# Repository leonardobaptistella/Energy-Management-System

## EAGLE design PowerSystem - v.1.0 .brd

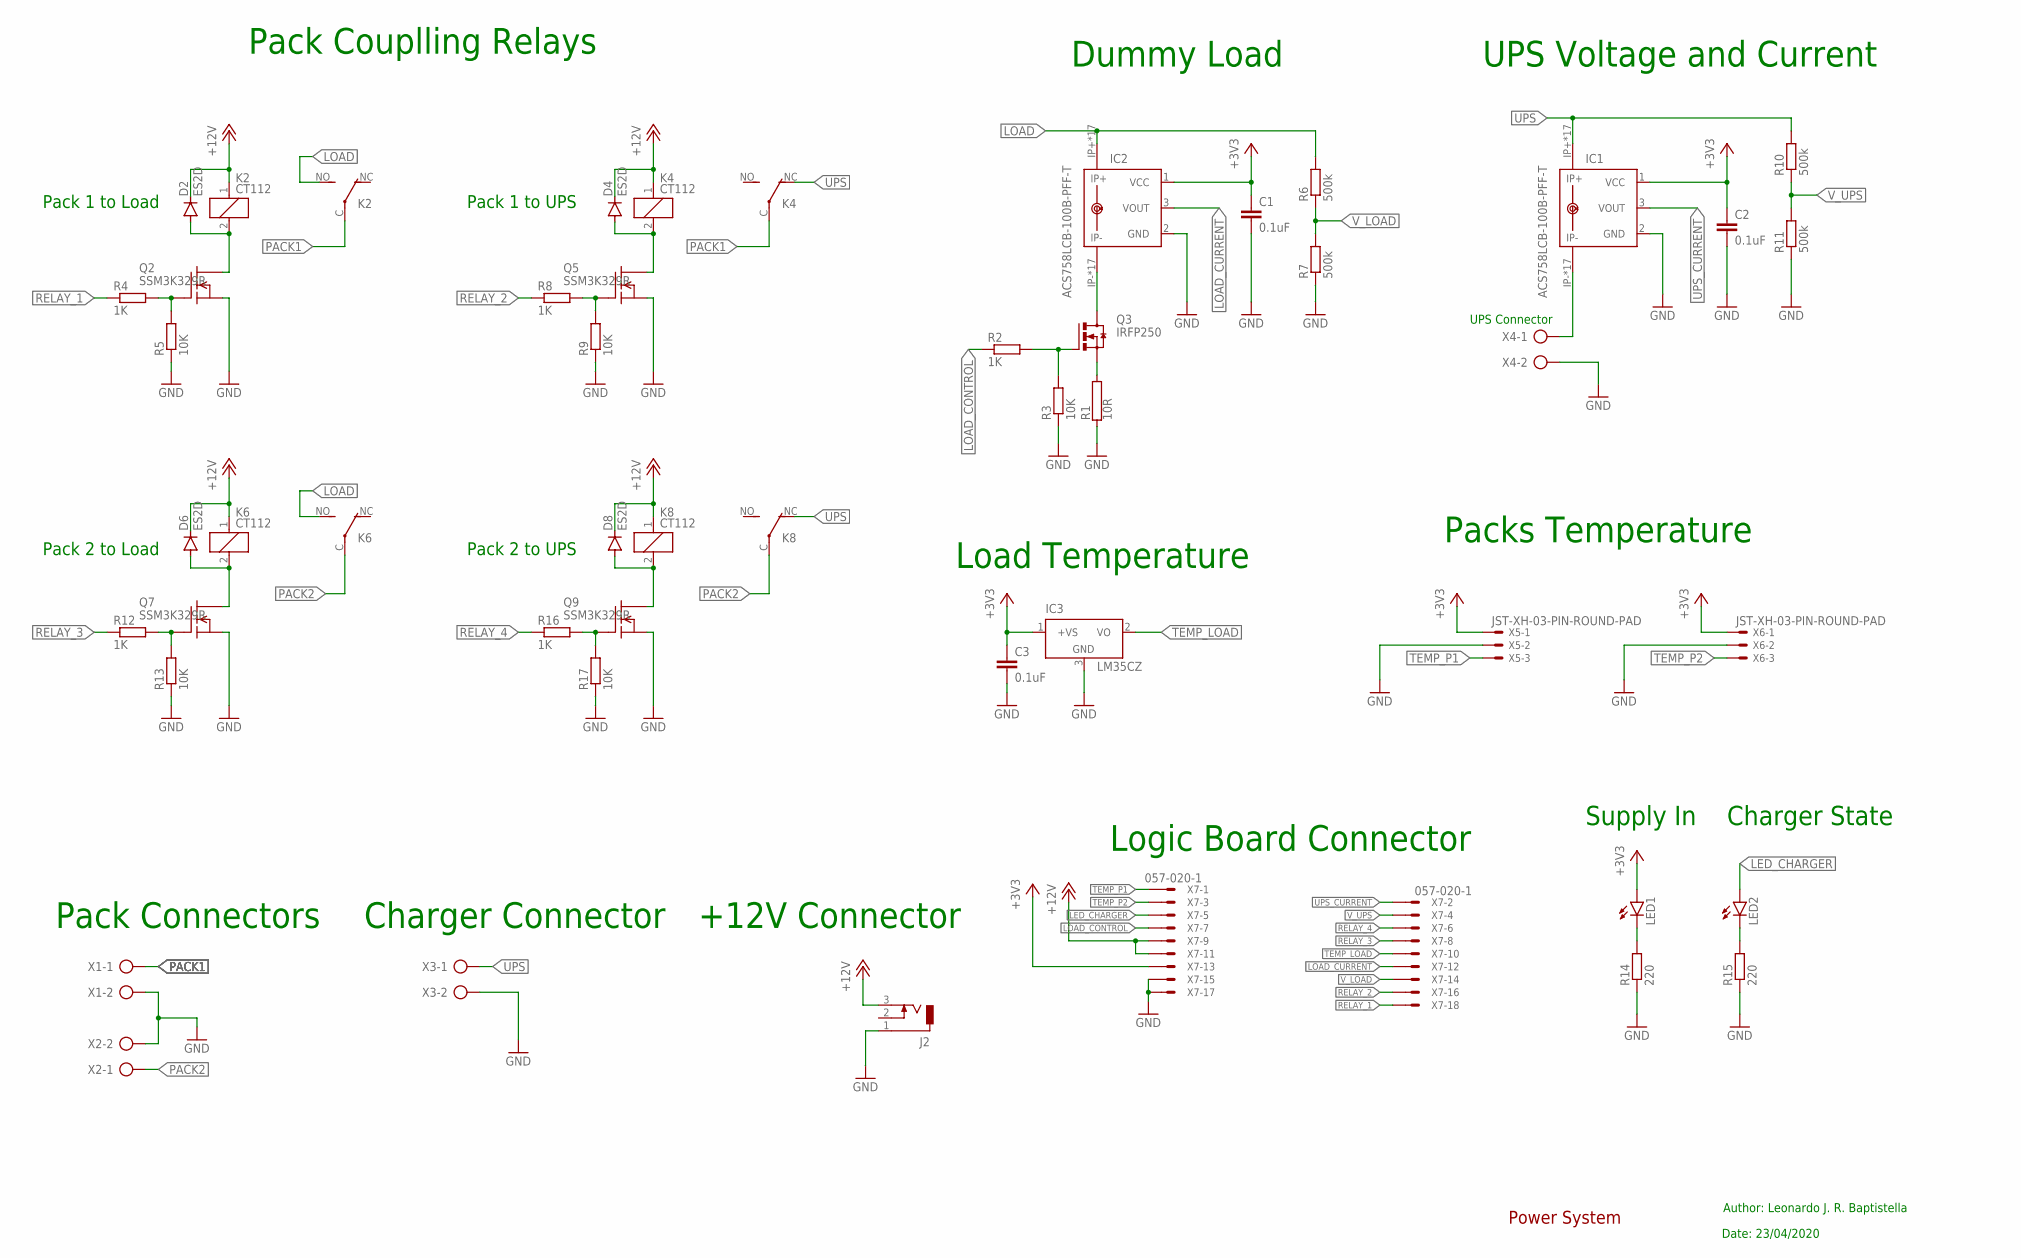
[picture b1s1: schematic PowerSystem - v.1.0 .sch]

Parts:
C1, C2, C3: 0.1uF; C1206
D2, D4, D6, D8: ES2D; SMB
IC1, IC2: ACS758LCB-100B-PFF-T; CB-PFF
IC3: LM35CZ; TO92
J2: DCJ0303
K2, K4, K6, K8: CT112; CT-SLIM
LED1, LED2: LEDCHIPLED_1206; CHIPLED_1206
Q2, Q5, Q7, Q9: SSM3K329R; SOT23
Q3: IRFP250; TO-247AD-V
R1: 10R; HS25
R2, R4, R8, R12, R16: 1K; R1206
R3, R5, R9, R13, R17: 10K; R1206
R6, R7, R10, R11: 500k; R1206
R14, R15: 220; R1206
X1, X2, X3, X4: AK500/2-H
X5, X6: JST-XH-03-PIN-ROUND-PAD; JST-XH-03-PACKAGE-ROUND-PAD
X7: 057-020-1

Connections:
+3V3: C1.1, C2.1, C3.1, IC1.1 (VCC), IC2.1 (VCC), IC3.1 (+VS), LED1.A, X5.1, X6.1, X7.13
+12V: D2.C, D4.C, D6.C, D8.C, J2.3, K2.1, K4.1, K6.1, K8.1, X7.9, X7.11
GND: C1.2, C2.2, C3.2, IC1.2 (GND), IC2.2 (GND), IC3.3 (GND), J2.1, Q2.2 (S), Q5.2 (S), Q7.2 (S), Q9.2 (S), R1.1, R3.1, R5.1, R7.1, R9.1, R11.1, R13.1, R14.1, R15.1, R17.1, X1.2, X2.2, X3.2, X4.2, X5.2, X6.2, X7.15, X7.17
LED_CHARGER: LED2.A, X7.5
LOAD: IC2.IP+, IC2.IP+@2 (IP+), IC2.IP+@3 (IP+), IC2.IP+@4 (IP+), IC2.IP+@5 (IP+), IC2.IP+@6 (IP+), IC2.IP+@7 (IP+), IC2.IP+@8 (IP+), IC2.IP+@9 (IP+), IC2.IP+@10 (IP+), IC2.IP+@11 (IP+), IC2.IP+@12 (IP+), IC2.IP+@13 (IP+), IC2.IP+@14 (IP+), IC2.IP+@15 (IP+), IC2.IP+@16 (IP+), IC2.IP+@17 (IP+), K2.NO (S), K6.NO (S), R6.2
LOAD_CONTROL: R2.1, X7.7
LOAD_CURRENT: IC2.3 (VOUT), X7.12
unnamed: Q3.S, R1.2
unnamed: Q2.1 (G), R4.2, R5.2
unnamed: Q3.G, R2.2, R3.2
unnamed: D2.A, K2.2, Q2.3 (D)
unnamed: IC2.IP-, IC2.IP-@2 (IP-), IC2.IP-@3 (IP-), IC2.IP-@4 (IP-), IC2.IP-@5 (IP-), IC2.IP-@6 (IP-), IC2.IP-@7 (IP-), IC2.IP-@8 (IP-), IC2.IP-@9 (IP-), IC2.IP-@10 (IP-), IC2.IP-@11 (IP-), IC2.IP-@12 (IP-), IC2.IP-@13 (IP-), IC2.IP-@14 (IP-), IC2.IP-@15 (IP-), IC2.IP-@16 (IP-), IC2.IP-@17 (IP-), Q3.D
unnamed: Q5.1 (G), R8.2, R9.2
unnamed: D4.A, K4.2, Q5.3 (D)
unnamed: IC1.IP-, IC1.IP-@2 (IP-), IC1.IP-@3 (IP-), IC1.IP-@4 (IP-), IC1.IP-@5 (IP-), IC1.IP-@6 (IP-), IC1.IP-@7 (IP-), IC1.IP-@8 (IP-), IC1.IP-@9 (IP-), IC1.IP-@10 (IP-), IC1.IP-@11 (IP-), IC1.IP-@12 (IP-), IC1.IP-@13 (IP-), IC1.IP-@14 (IP-), IC1.IP-@15 (IP-), IC1.IP-@16 (IP-), IC1.IP-@17 (IP-), X4.1
unnamed: LED2.C, R15.2
unnamed: Q7.1 (G), R12.2, R13.2
unnamed: D6.A, K6.2, Q7.3 (D)
unnamed: LED1.C, R14.2
unnamed: Q9.1 (G), R16.2, R17.2
unnamed: D8.A, K8.2, Q9.3 (D)
PACK1: K2.C, K4.C, X1.1
PACK2: K6.C, K8.C, X2.1
RELAY_1: R4.1, X7.18
RELAY_2: R8.1, X7.16
RELAY_3: R12.1, X7.8
RELAY_4: R16.1, X7.6
TEMP_LOAD: IC3.2 (VO), X7.10
TEMP_P1: X5.3, X7.1
TEMP_P2: X6.3, X7.3
UPS: IC1.IP+, IC1.IP+@2 (IP+), IC1.IP+@3 (IP+), IC1.IP+@4 (IP+), IC1.IP+@5 (IP+), IC1.IP+@6 (IP+), IC1.IP+@7 (IP+), IC1.IP+@8 (IP+), IC1.IP+@9 (IP+), IC1.IP+@10 (IP+), IC1.IP+@11 (IP+), IC1.IP+@12 (IP+), IC1.IP+@13 (IP+), IC1.IP+@14 (IP+), IC1.IP+@15 (IP+), IC1.IP+@16 (IP+), IC1.IP+@17 (IP+), K4.NC (O), K8.NC (O), R10.2, X3.1
UPS_CURRENT: IC1.3 (VOUT), X7.2
V_LOAD: R6.1, R7.2, X7.14
V_UPS: R10.1, R11.2, X7.4

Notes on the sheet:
Pack Couplling Relays
Dummy Load
Pack Connectors
Pack 1 to Load
Pack 1 to UPS
Pack 2 to Load
Pack 2 to UPS
Charger Connector
UPS Connector
UPS Voltage and Current
Packs Temperature
+12V Connector
Load Temperature
Supply In
Charger State
Logic Board Connector
Author: Leonardo J. R. Baptistella
Date: 23/04/2020
Power System

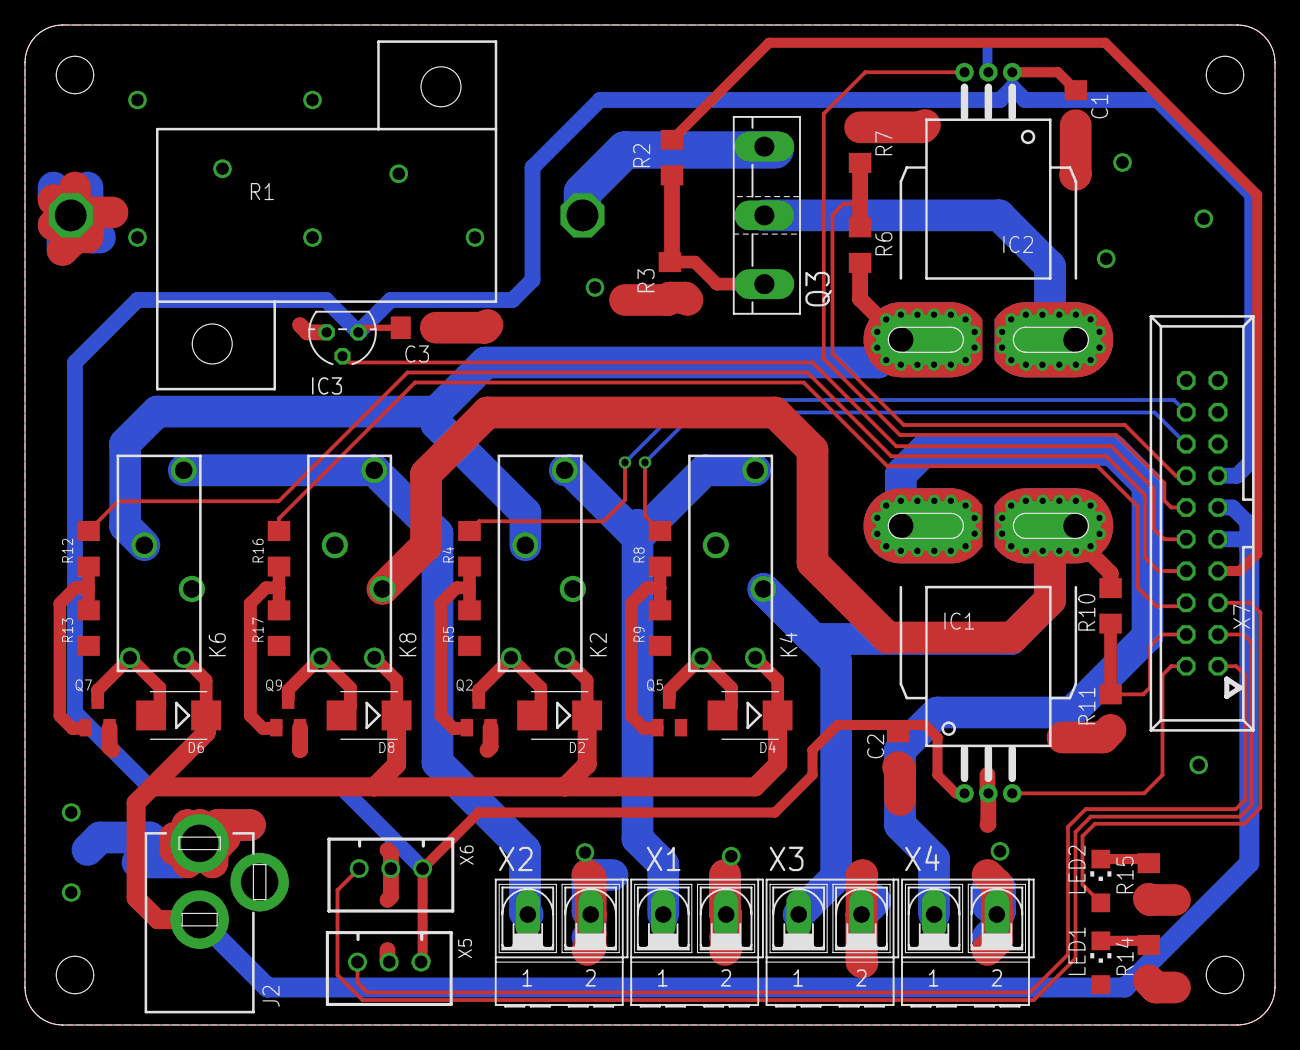
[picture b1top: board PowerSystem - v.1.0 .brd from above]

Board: 2 copper layers, 100.0 x 80.0 mm, 46 parts (0 on the bottom side), 34 nets.

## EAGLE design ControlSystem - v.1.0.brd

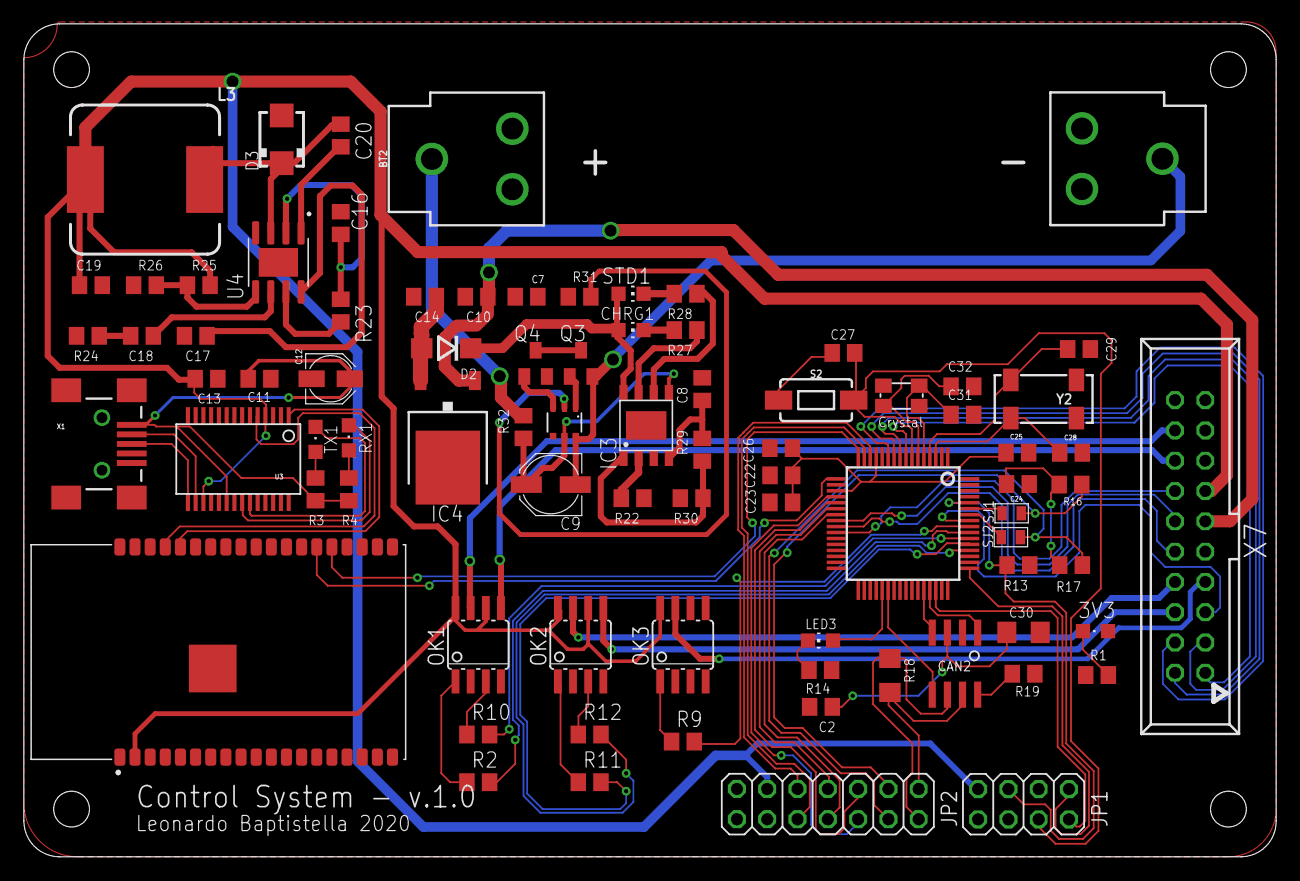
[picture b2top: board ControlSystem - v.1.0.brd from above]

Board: 2 copper layers, 105.0 x 69.8 mm, 82 parts (0 on the bottom side), 85 nets.

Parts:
3V3: CHIPLED_0805
A1: ESP32-WROVER-I; XCVR_ESP32-WROVER-I
BT2: BATTERY_18650-HOLDER
C2, C22, C23, C24, C25, C26, C27, C28, C29, C31, C32: C0805
C7: 10uf; C0805
C8, C10, C14, C16: 10uF; C0805
C9: 0.1uF; PANASONIC_C
C11, C13, C17: 0.1uF; C0805
C12: 10uF; PANASONIC_B
C18: 3.9nF; C0805
C19: 22uF; C0805
C20: 10nF; C0805
C30: 1nF; C1206
CAN2: SN65HVD233D; SOIC8
CHRG1: CHIP-LED0805
COMM_MICRO1: STM32L496RGT6; LQFP64_10X10
D2: DO214BA
D3: B130-13-F; SMA
IC3: TP4056; SOP-8
IC4: 7806DT; TO252
JP1: 2X04
JP2: 2X07
L3: SRR1280
LED3: CHIP-LED0805
OK1, OK2, OK3: ILD205; SOIC08
Q3, Q4: SSM3K329R; SOT23
R1: 220; R0805
R2, R3, R4, R9, R10, R11, R12: 1K; R0805
R13, R14, R16, R17, R22, R29, R30: R0805
R18: 120; R1206
R19, R32: 100; R0805
R23: 100K; R0805
R24: 6.8K; R0805
R25: 26.1K; R0805
R26: 10K; R0805
R27, R28, R31: 1k; R0805
RX1: Green; CHIPLED_0805
S2: MOMENTARY-SWITCH-SPST-SMD-6.0X3.5MM; TACTILE_SWITCH_SMD_6.0X3.5MM
SJ1, SJ2: SMD-JUMPER-2
STD1: CHIP-LED0805
TX1: Red; CHIPLED_0805
U3: FT232RLSSOP; SSOP28DB
U4: MP2307DN-LF-Z; SOIC127P600X170-9N
U$2: CRYSTAL; CRYSTAL_SMD
U$3: DW01; SOT23-6
X1: USB-SMD-NS; USB-MINIB-NOSTOP
X7: 057-020-1
Y2: CRYSTAL_8X3.8

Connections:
+3V3: 3V3.A, A1.2, C2.1, C13.1, C19.1, C22.1, C23.1, C24.1, C25.1, C26.1, C30.1, CAN2.3, COMM_MICRO1.1, COMM_MICRO1.13, COMM_MICRO1.19, COMM_MICRO1.32, COMM_MICRO1.48, COMM_MICRO1.64, JP1.7, JP2.11, L3.2, OK1.6, OK1.8, OK2.6, OK2.8, OK3.8, R16.2, R17.2, R25.2, U3.4, U3.17, X7.13
+5V: C8.1, C11.1, C12.+, CHRG1.A, D2.C, IC3.4, IC3.8, R3.2, R4.2, R29.2, STD1.A, U3.20, X1.VBUS
+12V: C10.1, IC4.1, X7.9, X7.11
BAT+: C7.1, C9.+, C16.1, IC3.5, R23.2, R32.1, U4.2, U$3.5
BOOT: COMM_MICRO1.60, JP1.5, R13.1
CAN1_LBK: CAN2.5, COMM_MICRO1.38
CAN1_RX: CAN2.4, COMM_MICRO1.44
CAN1_TX: CAN2.1, COMM_MICRO1.45
CAN_H: CAN2.7, JP2.1, R18.1
CAN_L: CAN2.6, JP2.2, R18.2
GND: A1.1, A1.15, A1.38, C2.2, C7.2, C8.2, C10.2, C11.2, C12.-, C13.2, C14.2, C16.2, C17.2, C19.2, C22.2, C23.2, C24.2, C25.2, C26.2, C27.1, C28.1, C29.1, C30.2, C31.2, C32.2, CAN2.2, COMM_MICRO1.12, COMM_MICRO1.18, COMM_MICRO1.31, COMM_MICRO1.47, COMM_MICRO1.63, D3.A, IC3.3, IC4.3, JP1.6, JP1.8, JP2.13, OK1.2, OK1.4, OK2.2, OK2.4, OK3.2, Q4.2, R1.1, R13.2, R14.1, R19.1, R22.1, R24.1, R26.1, R30.1, R31.1, S2.1, U3.7, U3.18, U3.21, U3.25, U3.26, U4.4, U$2.P$1, U$2.P$4, X1.GND, X7.15, X7.17
LED_CHARGER: COMM_MICRO1.57, X7.5
LOAD_CONTROL: OK3.7, X7.7
LOAD_CURRENT: COMM_MICRO1.24, X7.12
MISO_BUS: COMM_MICRO1.22, JP2.7
MOSI_BUS: COMM_MICRO1.23, JP2.8
M_LOAD_CONTROL: COMM_MICRO1.56, R9.2
M_RELAY_1: COMM_MICRO1.55, R2.2
M_RELAY_2: COMM_MICRO1.54, R10.2
M_RELAY_3: COMM_MICRO1.53, R11.2
M_RELAY_4: COMM_MICRO1.52, R12.2
unnamed: 3V3.C, R1.2
unnamed: R3.1, TX1.A
unnamed: R4.1, RX1.A
unnamed: OK1.1, R2.1
unnamed: OK3.1, R9.1
unnamed: OK1.3, R10.1
unnamed: OK2.1, R11.1
unnamed: OK2.3, R12.1
unnamed: COMM_MICRO1.37, LED3.A
unnamed: LED3.C, R14.2
unnamed: C28.2, COMM_MICRO1.3, Y2.P$1
unnamed: C29.2, COMM_MICRO1.4, Y2.P$4
unnamed: COMM_MICRO1.59, SJ1.1
unnamed: COMM_MICRO1.58, SJ2.1
unnamed: CAN2.8, R19.2
unnamed: IC3.2, R22.2
unnamed: R23.1, U4.7
unnamed: C18.2, R24.2
unnamed: C17.1, U4.8
unnamed: C18.1, U4.6
unnamed: C20.1, D3.C, L3.1, U4.3
unnamed: R25.1, R26.2, U4.5
unnamed: C20.2, U4.1
unnamed: IC3.7, R27.1
unnamed: IC3.6, R28.1
unnamed: CHRG1.C, R27.2
unnamed: R28.2, STD1.C
unnamed: IC3.1, R29.1, R30.2
unnamed: R31.2, U$3.2
unnamed: Q3.1, U$3.1
unnamed: Q3.3, Q4.3
unnamed: Q4.1, U$3.3
unnamed: BT2.PWR@1, R32.2
unnamed: BT2.GND@1, C9.-, Q3.2, U$3.6
unnamed: C14.1, D2.A, IC4.2
NRST: C27.2, COMM_MICRO1.7, JP1.4, S2.2
NSS_BUS: COMM_MICRO1.20, JP2.6
OSC_IN: C31.1, COMM_MICRO1.5, U$2.P$2
OSC_OUT: C32.1, COMM_MICRO1.6, U$2.P$3
RELAY_1: OK1.7, X7.18
RELAY_2: OK1.5, X7.16
RELAY_3: OK2.7, X7.8
RELAY_4: OK2.5, X7.6
RXDO: A1.34, U3.1
RXLED: RX1.C, U3.22
SCLK_BUS: COMM_MICRO1.21, JP2.5
SCL_BUS: JP2.4, R17.1, SJ2.2
SDA_BUS: JP2.3, R16.1, SJ1.2
SWCLK: COMM_MICRO1.49, JP1.1
SWDIO: COMM_MICRO1.46, JP1.2
TEMP_LOAD: COMM_MICRO1.25, X7.10
TEMP_P1: COMM_MICRO1.8, X7.1
TEMP_P2: COMM_MICRO1.9, X7.3
TXDO: A1.35, U3.5
TXLED: TX1.C, U3.23
UART_RX: A1.25, COMM_MICRO1.17
UART_RX_BUS: COMM_MICRO1.15, JP2.10
UART_TX: A1.24, COMM_MICRO1.16
UART_TX_BUS: COMM_MICRO1.14, JP2.9
UPS_CURRENT: COMM_MICRO1.10, X7.2
USB_D+1: U3.15, X1.D+
USB_D-1: U3.16, X1.D-
V_LOAD: COMM_MICRO1.26, X7.14
V_UPS: COMM_MICRO1.11, X7.4

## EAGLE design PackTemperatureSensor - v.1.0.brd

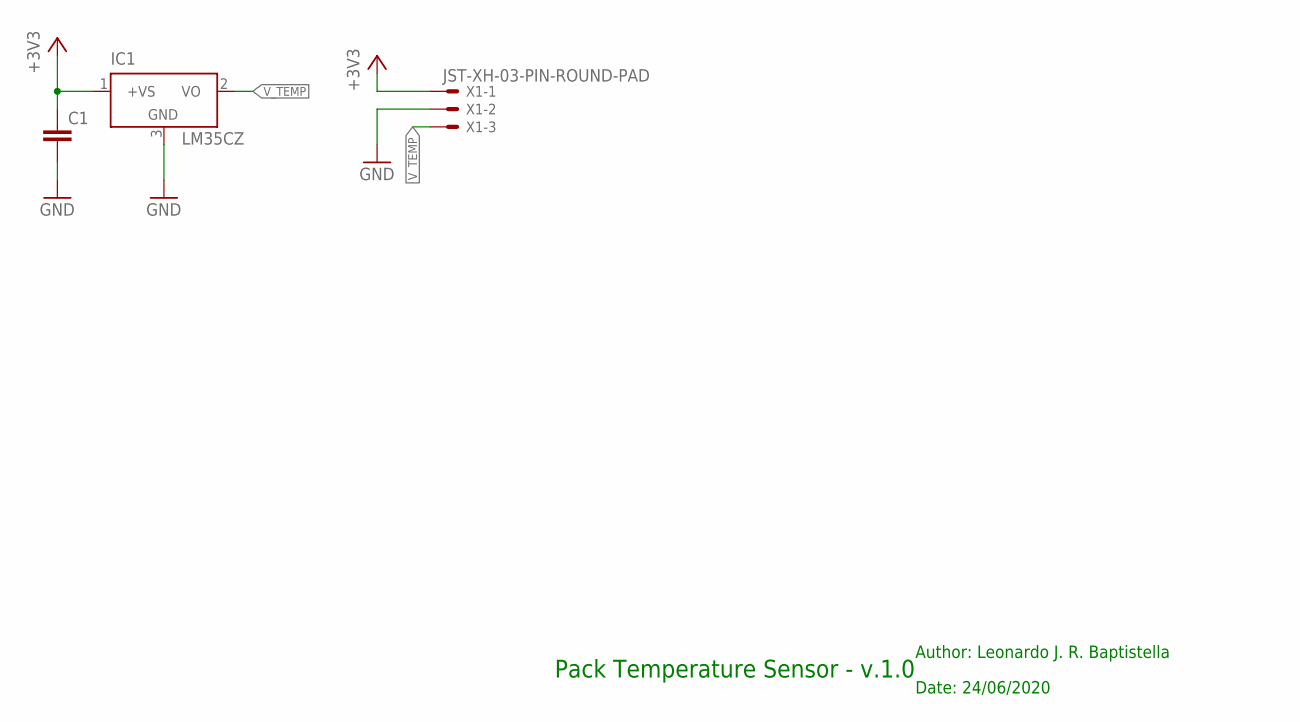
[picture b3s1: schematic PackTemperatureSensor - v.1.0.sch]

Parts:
C1: C-EUC1206; C1206
IC1: LM35CZ; TO92
X1: JST-XH-03-PIN-ROUND-PAD; JST-XH-03-PACKAGE-ROUND-PAD

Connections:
+3V3: C1.1, IC1.1 (+VS), X1.1
GND: C1.2, IC1.3 (GND), X1.2
V_TEMP: IC1.2 (VO), X1.3

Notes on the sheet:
Pack Temperature Sensor - v.1.0
Author: Leonardo J. R. Baptistella
Date: 24/06/2020

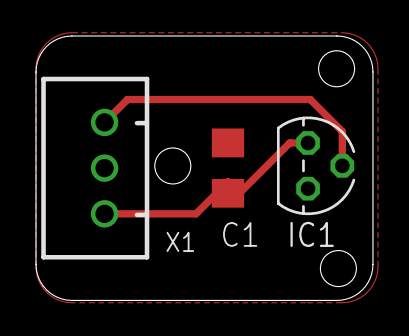
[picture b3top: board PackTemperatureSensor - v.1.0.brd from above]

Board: 2 copper layers, 18.7 x 14.7 mm, 3 parts (0 on the bottom side), 3 nets.

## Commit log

2020-07-07 Boards

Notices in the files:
parts and their libraries:
SparkFun-Switches: Licensing: Creative Commons ShareAlike 4.0 International - https://creativecommons.org/licenses/by-sa/4.0
FaBo-PIN: Released under the Creative Commons Attribution-ShareAlike 4.0 License
https://creativecommons.org/licenses/by-sa/4.0
inductor-bourns: Copyright (C) 2008, Bob Starr
